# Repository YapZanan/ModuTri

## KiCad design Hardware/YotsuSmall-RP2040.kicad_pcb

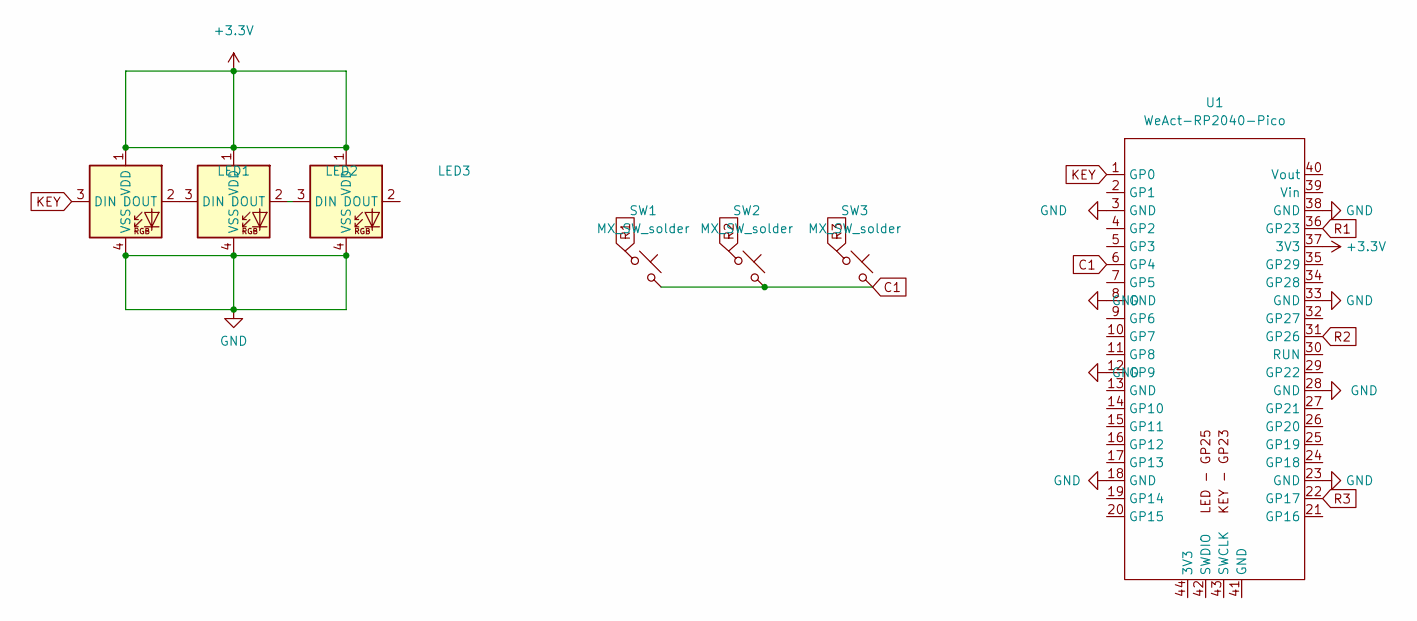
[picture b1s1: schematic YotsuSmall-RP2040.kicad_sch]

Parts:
LED1, LED2, LED3: MX_SK6812MINI-E; LED_MX_6028R
SW1, SW2, SW3: MX_SW_solder; SW_MX_1u
U1: WeAct-RP2040-Pico

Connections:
+3.3V: LED1.1 (VDD), LED2.1 (VDD), LED3.1 (VDD), U1.37 (3V3)
C1: SW1.2, SW2.2, SW3.2, U1.6 (GP4)
GND: LED1.4 (VSS), LED2.4 (VSS), LED3.4 (VSS), U1.3 (GND), U1.8 (GND), U1.12 (GP9), U1.18 (GND), U1.23 (GND), U1.28 (GND), U1.33 (GND), U1.38 (GND)
KEY: LED1.3 (DIN), U1.1 (GP0)
unnamed: LED1.2 (DOUT), LED2.3 (DIN)
unnamed: LED2.2 (DOUT), LED3.3 (DIN)
R1: SW1.1, U1.36 (GP23)
R2: SW2.1, U1.31 (GP26)
R3: SW3.1, U1.22 (GP17)

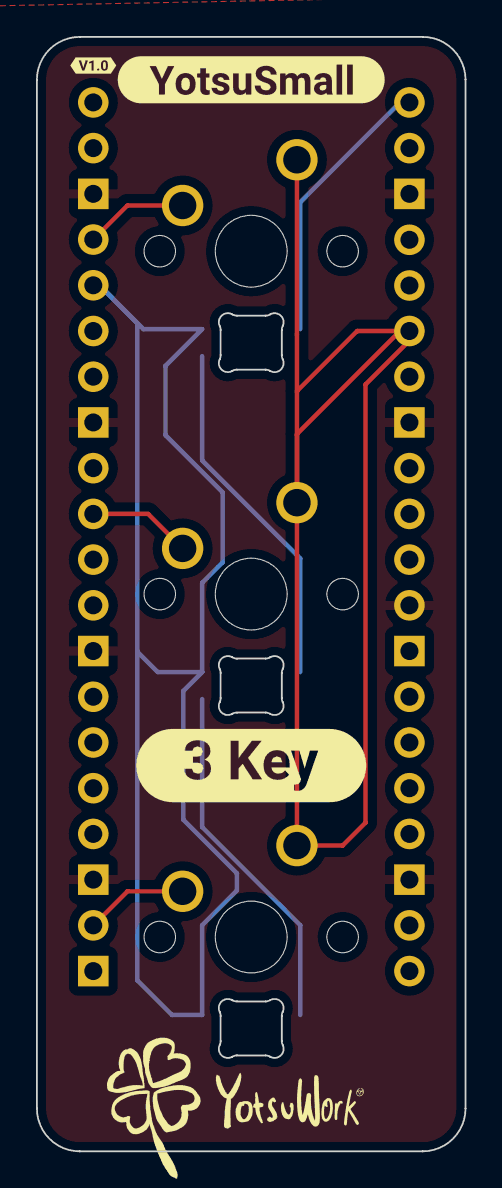
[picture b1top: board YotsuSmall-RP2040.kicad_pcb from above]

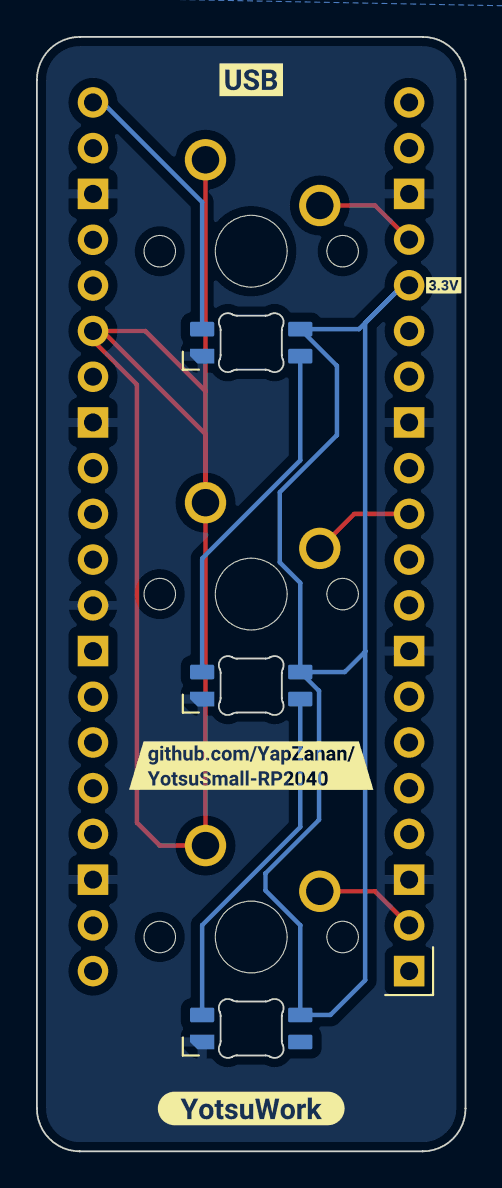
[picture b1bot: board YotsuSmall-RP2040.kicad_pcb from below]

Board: 2 copper layers, 23.8 x 61.9 mm, 14 parts (8 on the bottom side), 9 nets.

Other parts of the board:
kibuzzard-640FDD0C: G***; kibuzzard-640FDD0C
kibuzzard-640FDD6A: G***; kibuzzard-640FDD6A
kibuzzard-640FDDAE: G***; kibuzzard-640FDDAE
kibuzzard-640FE15A: G***; kibuzzard-640FE15A
kibuzzard-641144B7: G***; kibuzzard-641144B7
kibuzzard-64114471: G***; kibuzzard-64114471
kibuzzard-64114494: G***; kibuzzard-64114494

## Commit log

2023-03-16 Add PCB design files for YotsuSmall-RP2040
2023-03-16 Software
2023-03-16 add software
2023-03-16 add PEG
2023-03-16 add detail on PCB
2023-03-20 ChangeName
